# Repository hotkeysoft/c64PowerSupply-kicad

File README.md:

# C64 Power Supply
Rev B September 2022

### Basic Tests: complete

This was version was built and tested 40 minutes @ 2.5A on the 5V line with no issue. 
- Heat dissipation could be a problem in an plastic enclosure, will need more tests.
  - Regulator dissipates heat through ground plane so a metal case (and metal stand-offs) could be enough

### Simple Switching Power Supply
- 120/240VAC Input (toggle with jumpers)
- Beefier transformer (56VA)
- TVS diodes on both transformer output lines (optional)
- MOV and filtering cap on input side (optional)
- 9VAC Output 1.5A Max w/Fuse
- 5VDC Output 3A Max w/Fuse, more than enough for C128
- +5V Adjustable with trimmer
- BD9E303EFJ Buck switching regulator for +5V output
  - In theory more efficient than old LM2596T, tests will tell 
- Two terminal blocks to use the power supply with either a C64 or a C128
  - *NOT* at the same time...
    - 9VAC line should be fine in theory (transformer can provide 3A). Altough noise/crosstalk could be an issue.
    - 5V line could overload. The max capacity of this switching regulator is 3A. C128 uses around 2A by itself, with nothing connected. C64 is rated to use 1.5A. Not responsible if someone powers both at the same time.

Images
============
|Front                                                 | Back                                              |
|------------------------------------------------------|---------------------------------------------------|
|||

### Schematics (pdf)
- [Complete schematics](./img/schema.pdf)

### PCB Images (svg)
- [Top](./img/pcb-front.svg)
- [Bottom](./img/pcb-back.svg)

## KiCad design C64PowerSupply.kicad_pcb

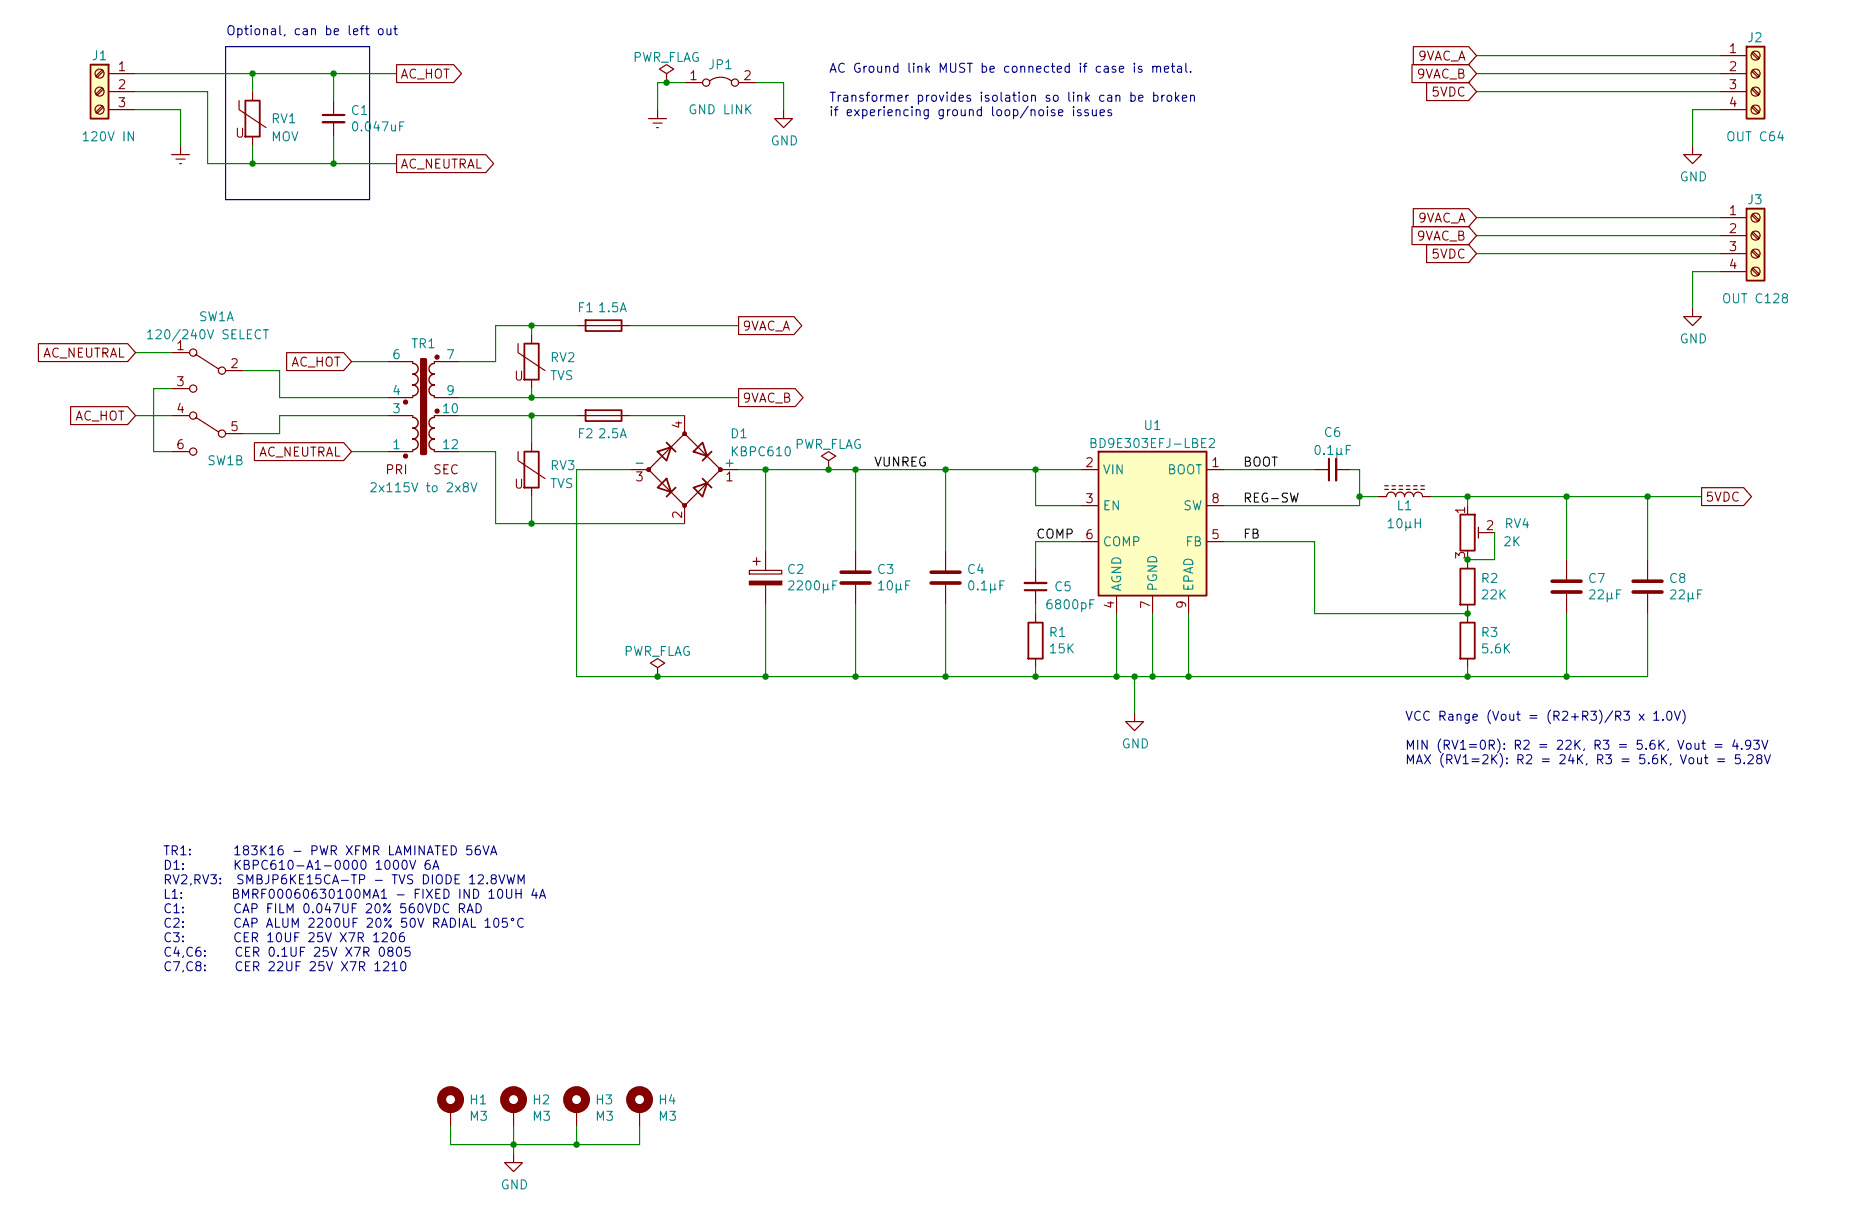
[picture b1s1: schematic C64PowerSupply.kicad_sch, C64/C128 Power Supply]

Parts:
C1: 0.047uF; C_Rect_L18.0mm_W5.0mm_P15.00mm_FKS3_FKP3
C2: 2200μF; CP_Radial_D16.0mm_P7.50mm
C3: 10μF; C_1206_3216Metric_Pad1.33x1.80mm_HandSolder
C4, C6: 0.1μF; C_0805_2012Metric_Pad1.18x1.45mm_HandSolder
C5: 6800pF; C_0805_2012Metric_Pad1.18x1.45mm_HandSolder
C7, C8: 22μF; C_1210_3225Metric_Pad1.33x2.70mm_HandSolder
D1: KBPC610; Diode_Bridge_15.1x15.1x6.3mm_P10.9mm
F1: 1.5A; Fuse_PTF-76
F2: 2.5A; Fuse_PTF-76
H1, H2, H3, H4: M3; MountingHole_3.2mm_M3_ISO7380_Pad
J1: 120V IN; TerminalBlock_Phoenix_PT-1,5-3-5.0-H_1x03_P5.00mm_Horizontal
J2: OUT C64; TerminalBlock_Phoenix_PT-1,5-4-5.0-H_1x04_P5.00mm_Horizontal
J3: OUT C128; TerminalBlock_Phoenix_PT-1,5-4-5.0-H_1x04_P5.00mm_Horizontal
JP1: GND LINK; SolderJumper-2_P1.3mm_Bridged_Pad1.0x1.5mm
L1: 10μH; L_BMRx00060630
R1: 15K; R_0805_2012Metric_Pad1.20x1.40mm_HandSolder
R2: 22K; R_0805_2012Metric_Pad1.20x1.40mm_HandSolder
R3: 5.6K; R_0805_2012Metric_Pad1.20x1.40mm_HandSolder
RV1: MOV; RV_Disc_D15.5mm_W3.9mm_P7.5mm
RV2, RV3: TVS; D_SMB
RV4: 2K; Potentiometer_Bourns_3296W_Vertical
SW1: 120/240V SELECT; V_SEL_SWITCH
TR1: 2x115V to 2x8V; Transformer_Hammond_183K16
U1: BD9E303EFJ-LBE2; Texas_HTSOP-8-1EP_3.9x4.9mm_P1.27mm_EP2.95x4.9mm_Mask2.4x3.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

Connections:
5VDC: C7.1, C8.1, J2.3, J3.3, L1.2, RV4.1
9VAC_A: F1.1, J2.1, J3.1
9VAC_B: J2.2, J3.2, RV2.2, TR1.9
/BOOT: C6.1, U1.1 (BOOT)
/COMP: C5.2, U1.6 (COMP)
/FB: R2.2, R3.1, U1.5 (FB)
/REG-SW: C6.2, L1.1, U1.8 (SW)
/VUNREG: C2.1, C3.1, C4.1, D1.1 (+), U1.2 (VIN), U1.3 (EN)
AC_HOT: C1.1, J1.1, RV1.1, SW1.4 (A), TR1.6
AC_NEUTRAL: C1.2, J1.2, RV1.2, SW1.1 (A), TR1.1
Earth: J1.3, JP1.1 (A)
GND: C2.2, C3.2, C4.2, C7.2, C8.2, D1.3 (-), H1.1, H2.1, H3.1, H4.1, J2.4, J3.4, JP1.2 (B), R1.2, R3.2, U1.4 (AGND), U1.7 (PGND), U1.9 (EPAD)
unnamed: C5.1, R1.1
unnamed: D1.2, RV3.2, TR1.12
unnamed: D1.4, F2.1
unnamed: F1.2, RV2.1, TR1.7
unnamed: F2.2, RV3.1, TR1.10
unnamed: R2.1, RV4.2, RV4.3
unnamed: SW1.2 (B), TR1.4
unnamed: SW1.3 (C), SW1.6 (C)
unnamed: SW1.5 (B), TR1.3

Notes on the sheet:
AC Ground link MUST be connected if case is metal. Transformer provides isolation so link can be broken if experiencing ground loop/noise issues
VCC Range (Vout = (R2+R3)/R3 x 1.0V) MIN (RV1=0R): R2 = 22K, R3 = 5.6K, Vout = 4.93V MAX (RV1=2K): R2 = 24K, R3 = 5.6K, Vout = 5.28V
TR1: 183K16 - PWR XFMR LAMINATED 56VA D1: KBPC610-A1-0000 1000V 6A RV2,RV3: SMBJP6KE15CA-TP - TVS DIODE 12.8VWM L1: BMRF00060630100MA1 - FIXED IND 10UH 4A C1: CAP FILM 0.047UF 20% 560VDC RAD C2: CAP ALUM 2200UF 20% 50V RADIAL 105°C C3: CER 10UF 25V X7R 1206 C4,C6: CER 0.1UF 25V X7R 0805 C7,C8: CER 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
Optional, can be left out

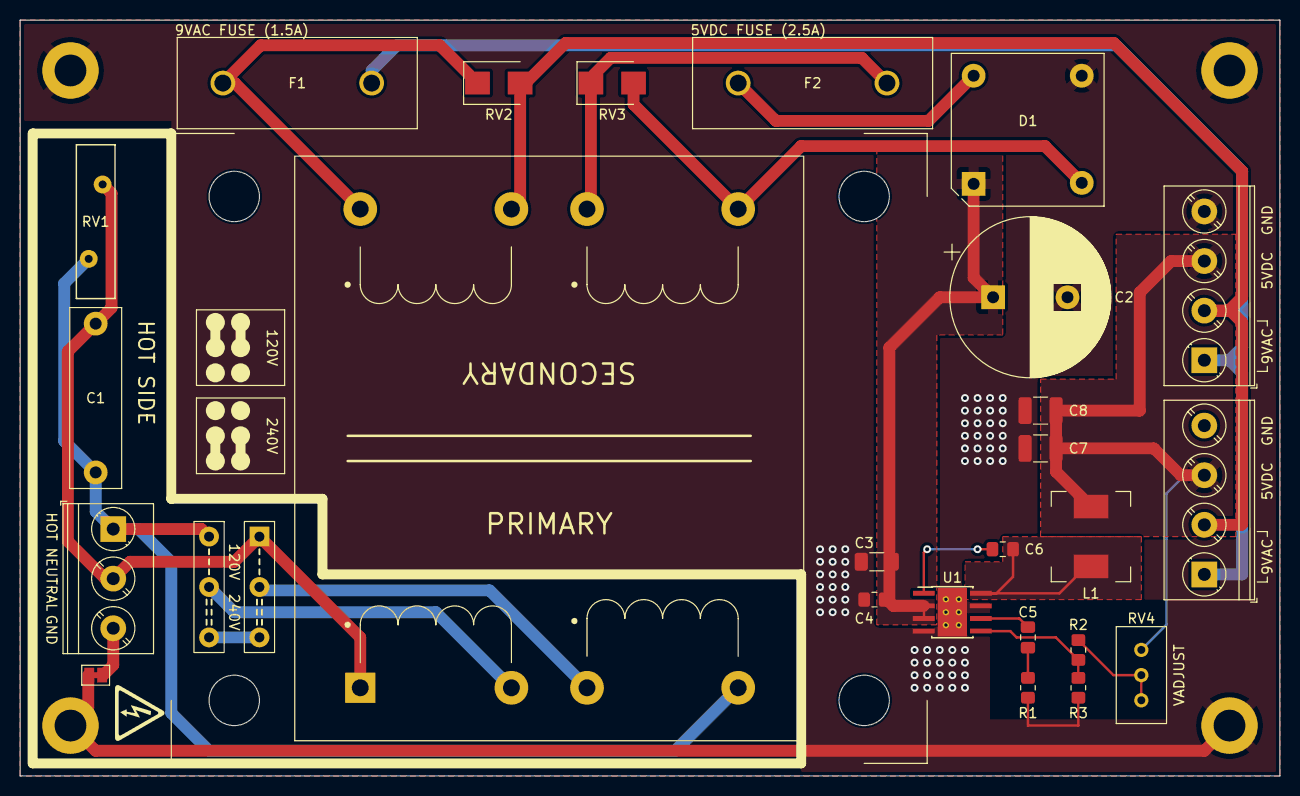
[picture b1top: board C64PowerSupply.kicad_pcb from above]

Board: 2 copper layers, 127.0 x 76.2 mm, 30 parts (0 on the bottom side), 21 nets.

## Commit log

2021-06-21 Schematic
2021-06-27 Footprints, layout
2021-06-27 Routing
2021-06-27 RevA Plot files
2021-07-01 Added trimpot. Routing
2021-07-01 Update plot
2021-07-01 Added images
2021-07-01 Add fab
2022-09-06 RevA - Update README
2022-09-06 Kicad6 upgrade
2022-09-18 Transformer hole size
2022-09-18 Cleanup, fix 120/240V switch
2022-09-18 Begin route
2022-09-18 Voltage sel switch footprint
2022-09-18 Move cap, add logo
2022-09-18 tweak
2022-09-18 Plot, images, README, Fix ground plane
2022-09-18 Fab outputs
2022-09-24 Bumped C2 to 2200uF
    1000uF worked fine @ 2A but regulation dropped quickly after
    because ripple was too large. 2200uF is enough to go up to 3A.
2022-09-24 README
2022-09-24 updated pdf
